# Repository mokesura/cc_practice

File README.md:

# CC Practice

※組み立て済みの写真に差し替え予定。

## 特徴
CC Practiceは、以下の特徴を持っています。

- 名刺サイズの6キーキーボード。
- マイコンにPro Microを使用。コンスルーによる抜き差しに対応。
- Cherry MX互換/Kailh Mid-Height/Kailh Choc V1/Kailh Choc V2/ALPS互換スイッチ対応。
  - Cherry MX互換/Kailh Mid-HeightスイッチはKailhソケットとはんだ付けの両方に対応。その他スイッチははんだ付けのみに対応。
- ダイオード不要の設計で、比較的簡単に組み立てを行うことができます（組み立てにははんだ付けが必要です）。
- QMK Firmware対応。
- [Remap](https://remap-keys.app)でのキーマップ変更に対応。

## 組み立て済みキーボードを手にした方向けの利用ガイド
組み立て済みのキーボードを受け取った方に向けた、利用ガイドを公開しております。

- [その1：事前説明編](https://note.com/azulee/n/n4eed2e0b9e5f)
- [その2：セットアップ編](https://note.com/azulee/n/n12c354e7c35d) 
- [その3：キー設定編](https://note.com/azulee/n/n925a49817ccf) 

## ファームウェア

- [QMK Firmware Sources](https://github.com/mokesura/qmk_firmware/tree/mokesura/cc_practice/keyboards/mokesura/cc_practice)
- [Hex File / Json for VIA](https://github.com/mokesura/cc_practice/tree/main/firmware)

## キーボードの入手方法
組み立て済みキーボードをBOOTHで頒布しております。

- [TRPGオンラインセッションで便利に使えるかもしれないミニキーボード（組立済）](https://azulee.booth.pm/items/4087407) 

### PCB & Plate Data
KiCadで作成した基板データ、プレートデータ。こちらのデータを使用して発注することもできます。

- [PCB & Gerber Data](https://github.com/mokesura/cc_practice/tree/main/pcb)
- [Plate Data](https://github.com/mokesura/cc_practice/tree/main/plate)

Kailh Mid-Heightスイッチ対応のFR-4プレートはまだ作れていません。

## 回路図
- [回路図/Schematic](https://github.com/mokesura/cc_practice/blob/main/pcb/cc-practice_Schematic.pdf)

## 組み立てに必要な部品リスト
公開予定。

## ライセンス
[MIT License](https://github.com/mokesura/cc_practice/blob/main/LICENSE)

## 使用したKiCadフットプリント
- [KBD - for building keyboard libraries](https://github.com/foostan/kbd) 

スイッチ部分のフットプリントは、上記ライブラリのものを改変して使用。公開予定。

## 連絡先
- 千葉千夏 / Chinatsu Chiba (azulee/mokesura)
  - Twitter: [@azulee](https://twitter.com/azulee)
  - E-Mail: mokesura@gmail.com

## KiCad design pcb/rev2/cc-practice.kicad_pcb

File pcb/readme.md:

# CC Practice PCB
Rev.1 By KiCad 5.1.10.
Rev.2 By KiCad 5.1.10.

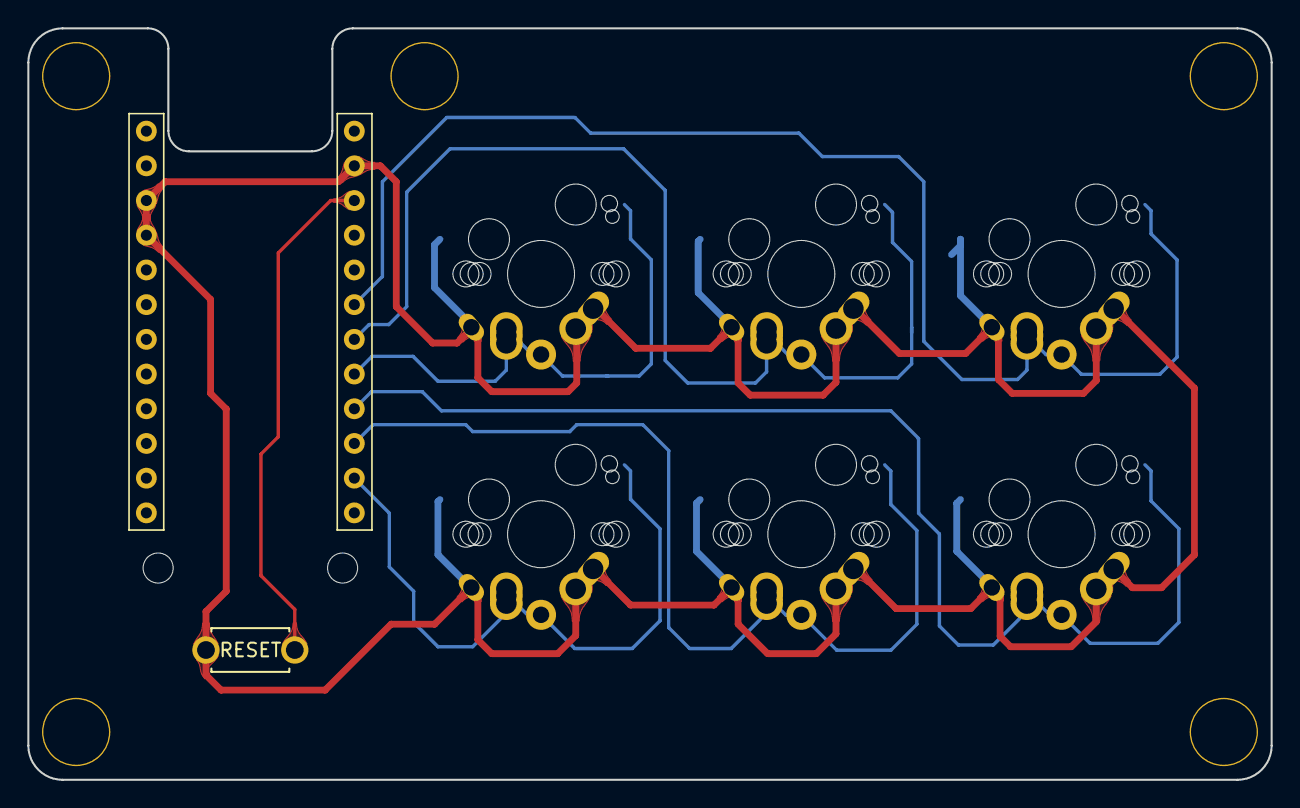
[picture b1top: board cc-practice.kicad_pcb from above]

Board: 2 copper layers, 91.0 x 55.0 mm, 15 parts (1 on the bottom side), 8 nets.

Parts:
RSW1: SW_Push; ResetSW_1side
S1, S2, S3, S4, S5: Screw_Terminal_01x01; HOLE
SW1, SW2, SW3, SW4, SW5, SW6: SW_PUSH; MX-MHeight-Hotswap_Choc12_Alps_v2
S_cover1, S_cover2: Screw_Terminal_01x01; thread_m2
U1: ProMicro_r; ProMicro_v3

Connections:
GND: RSW1.2, SW1.1, SW2.1, SW3.1, SW4.1, SW5.1, SW6.1, U1.3, U1.4, U1.23
Reset: RSW1.1, U1.22
SW1: SW1.2, U1.19
SW2: SW2.2, U1.18
SW3: SW3.2, U1.17
SW4: SW4.2, U1.16
SW5: SW5.2, U1.15
SW6: SW6.2, U1.14

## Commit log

2022-08-03 PCB Rev.1
2022-08-03 PCB Gerber-Data Rev.1
2022-08-03 Add PCB Rev.1 images.
2022-08-03 Build by QMK Firmware 0.17.6
2022-12-24 Build by QMK Firmware 0.18.17
2022-12-24 ダイスロールに対応
2022-12-25 PCB Rev.2 and Plate Data
